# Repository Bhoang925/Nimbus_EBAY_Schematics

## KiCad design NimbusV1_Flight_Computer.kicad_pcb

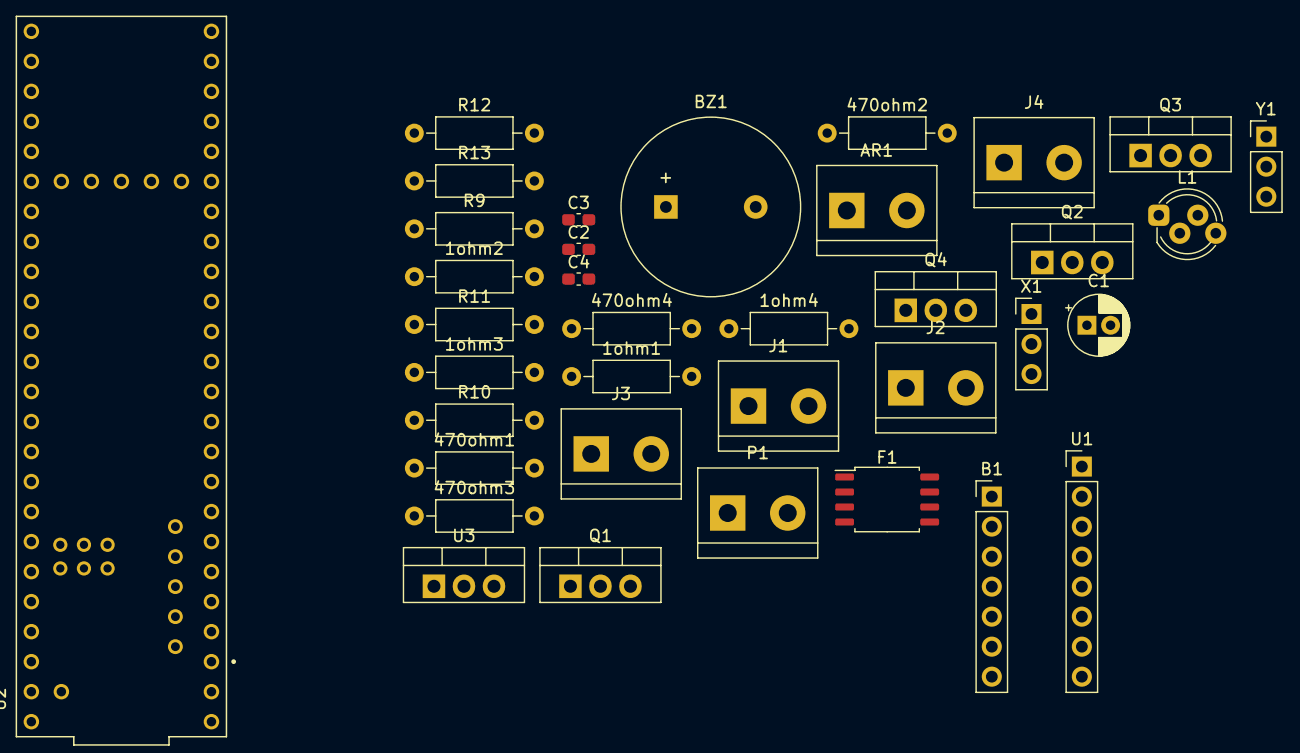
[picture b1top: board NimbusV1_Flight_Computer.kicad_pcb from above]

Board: 2 copper layers, 36 parts (0 on the bottom side), 35 nets, no tracks yet.

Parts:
1ohm1: R1; R_Axial_DIN0207_L6.3mm_D2.5mm_P10.16mm_Horizontal
1ohm2: R3; R_Axial_DIN0207_L6.3mm_D2.5mm_P10.16mm_Horizontal
1ohm3: R5; R_Axial_DIN0207_L6.3mm_D2.5mm_P10.16mm_Horizontal
1ohm4: R7; R_Axial_DIN0207_L6.3mm_D2.5mm_P10.16mm_Horizontal
470ohm1: R2; R_Axial_DIN0207_L6.3mm_D2.5mm_P10.16mm_Horizontal
470ohm2: R4; R_Axial_DIN0207_L6.3mm_D2.5mm_P10.16mm_Horizontal
470ohm3: R6; R_Axial_DIN0207_L6.3mm_D2.5mm_P10.16mm_Horizontal
470ohm4: R8; R_Axial_DIN0207_L6.3mm_D2.5mm_P10.16mm_Horizontal
AR1: ARMING SWITCH; TerminalBlock_bornier-2_P5.08mm
B1: BMP280; PinHeader_1x07_P2.54mm_Vertical
BZ1: Buzzer; Buzzer_15x7.5RM7.6
C1: 10uf; CP_Radial_D5.0mm_P2.00mm
C2, C3, C4: 1uf; C_0603_1608Metric_Pad1.08x0.95mm_HandSolder
F1: W25Q128JVS; SOIC-8_5.23x5.23mm_P1.27mm
J1: Pyro1; TerminalBlock_bornier-2_P5.08mm
J2: Pyro2; TerminalBlock_bornier-2_P5.08mm
J3: Pyro3; TerminalBlock_bornier-2_P5.08mm
J4: Pyro4; TerminalBlock_bornier-2_P5.08mm
L1: LED_ARGB; LED_D5.0mm-4_RGB_Staggered_Pins
P1: PWR SWITCH; TerminalBlock_bornier-2_P5.08mm
Q1, Q2, Q3, Q4: IRF540N; TO-220-3_Vertical
R9: 40ohm; R_Axial_DIN0207_L6.3mm_D2.5mm_P10.16mm_Horizontal
R10, R11: 1ohm; R_Axial_DIN0207_L6.3mm_D2.5mm_P10.16mm_Horizontal
R12: 1Mohm; R_Axial_DIN0207_L6.3mm_D2.5mm_P10.16mm_Horizontal
R13: 100kohm; R_Axial_DIN0207_L6.3mm_D2.5mm_P10.16mm_Horizontal
U1: MPU-6050; PinHeader_1x08_P2.54mm_Vertical
U2: DEV-16771; MODULE_DEV-16771
U3: LM7805_TO220; TO-220-3_Vertical
X1: ServoX; PinHeader_1x03_P2.54mm_Vertical
Y1: ServoY; PinHeader_1x03_P2.54mm_Vertical

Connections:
+3V3: AR1.1, C3.1, C4.1, F1.8 (VCC)
+5V: X1.2 (+), Y1.2 (+)
+12V: J1.2, J2.2, J3.2, J4.2, P1.2, R12.1
GND: 470ohm1.1, 470ohm2.1, 470ohm3.1, 470ohm4.1, B1.1 (GND), BZ1.2 (+), C1.2, C2.2, C3.2, C4.2, F1.4 (GND), Q1.3 (S), Q2.3 (S), Q3.3 (S), Q4.3 (S), R13.1, U2.GND1 (GND), U2.GND2 (GND), U2.GND3 (GND), U2.GND4 (GND), U2.GND5 (GND), U2.USB_GND1 (USB_GND), U2.USB_GND2 (USB_GND), U3.2 (GND), X1.3 (-), Y1.3 (-)
unnamed: 1ohm1.1, Q1.2 (D)
unnamed: 1ohm1.2, J1.1
unnamed: 1ohm2.1, Q2.2 (D)
unnamed: 1ohm2.2, J2.1
unnamed: 1ohm3.1, Q3.2 (D)
unnamed: 1ohm3.2, J3.1
unnamed: 1ohm4.1, Q4.2 (D)
unnamed: 1ohm4.2, J4.1
unnamed: 470ohm1.2, Q1.1 (G), U2.0 (RX1)
unnamed: 470ohm2.2, Q2.1 (G), U2.1 (TX1)
unnamed: 470ohm3.2, Q3.1 (G), U2.7 (RX2)
unnamed: 470ohm4.2, Q4.1 (G), U2.8 (TX2)
unnamed: AR1.2, U2.35 (TX8)
unnamed: B1.3 (SDI), F1.6 (CLK), U2.18 (A4)
unnamed: B1.4 (SCK), U2.19 (A5)
unnamed: BZ1.1 (-), U2.34 (RX8)
unnamed: C1.1, P1.1, U3.1 (VI)
unnamed: C2.1, U2.VIN, U3.3 (VO)
unnamed: F1.1 (~CS), U2.10 (CS1)
unnamed: F1.2 (DO(IO1)), U2.3 (LRCLK2)
unnamed: F1.5 (DI(IO0)), U2.4 (BCLK2)
unnamed: L1.1 (A), U2.3.3V_1 (3.3V), U2.3.3V_2 (3.3V), U2.3.3V_3 (3.3V)
unnamed: L1.2 (RK), R9.2
unnamed: L1.3 (GK), R10.2
unnamed: L1.4 (BK), R11.2
unnamed: R9.1, U2.6 (OUT1D)
unnamed: R10.1, U2.9 (OUT1C)
unnamed: R11.1, U2.2 (OUT2)
unnamed: R12.2, R13.2, U2.41 (A17)
unnamed: U2.28 (RX7), Y1.1 (PWM)
unnamed: U2.29 (TX7), X1.1 (PWM)
